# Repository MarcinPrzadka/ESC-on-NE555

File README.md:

# ESC-on-NE555
Regulator Obrotów Wentylatora

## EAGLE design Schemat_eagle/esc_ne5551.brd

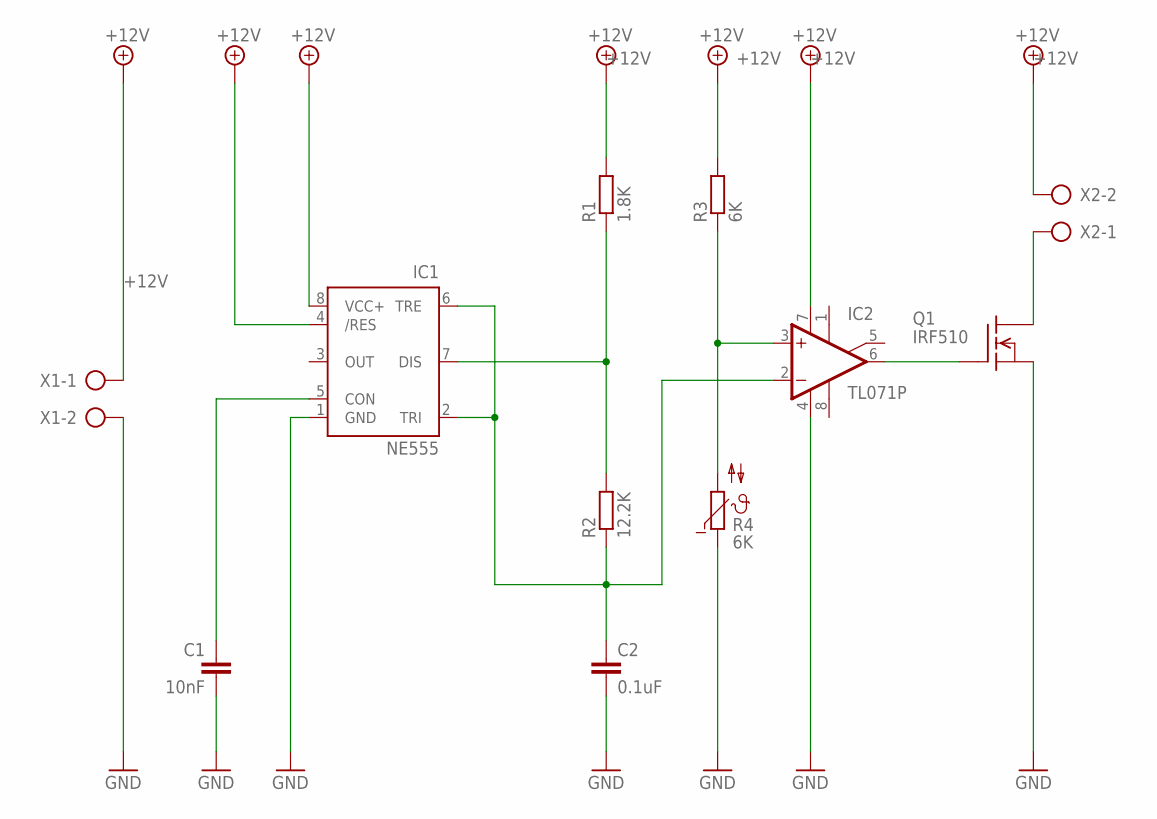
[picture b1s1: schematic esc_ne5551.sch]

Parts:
C1: 10nF; C025-025X050
C2: 0.1uF; C025-025X050
IC1: NE555; DIL-08
IC2: TL071P; DIL08
Q1: IRF510; TO220
R1: 1.8K; 0207/10
R2: 12.2K; 0207/10
R3: 6K; 0207/10
R4: 6K; P640
X1, X2: AK500/2

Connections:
+12V: IC1.4 (/RES), IC1.8 (VCC+), IC2.7 (V+), R1.2, R3.2, X1.1, X2.2
GND: C1.2, C2.2, IC1.1 (GND), IC2.4 (V-), Q1.3 (S), R4.1, X1.2
unnamed: IC1.7 (DIS), R1.1, R2.2
unnamed: IC2.3 (+IN), R3.1, R4.2
unnamed: Q1.2 (D), X2.1
unnamed: IC2.6 (OUT), Q1.1 (G)
unnamed: C1.1, IC1.5 (CON)
unnamed: C2.1, IC1.2 (TRI), IC1.6 (TRE), IC2.2 (-IN), R2.1

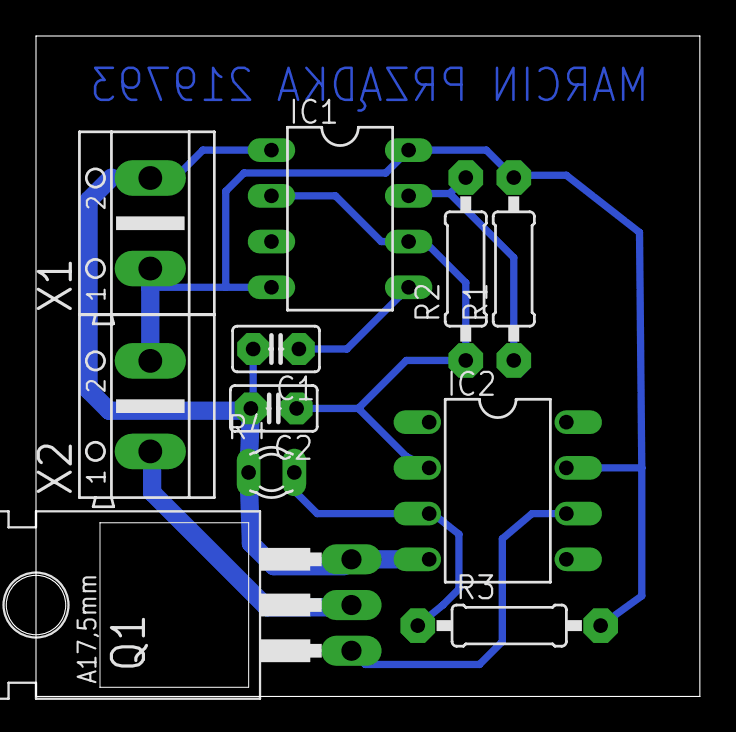
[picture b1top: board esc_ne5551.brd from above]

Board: 2 copper layers, 36.9 x 36.7 mm, 11 parts (0 on the bottom side), 8 nets.
